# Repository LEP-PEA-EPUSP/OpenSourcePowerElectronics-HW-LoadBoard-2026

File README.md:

# OpenSourcePowerElectronics-HW-LoadBoard-2026

This repository contains the manuals, schematics, layouts and other files necessary to build and used the AC and DC load boards.

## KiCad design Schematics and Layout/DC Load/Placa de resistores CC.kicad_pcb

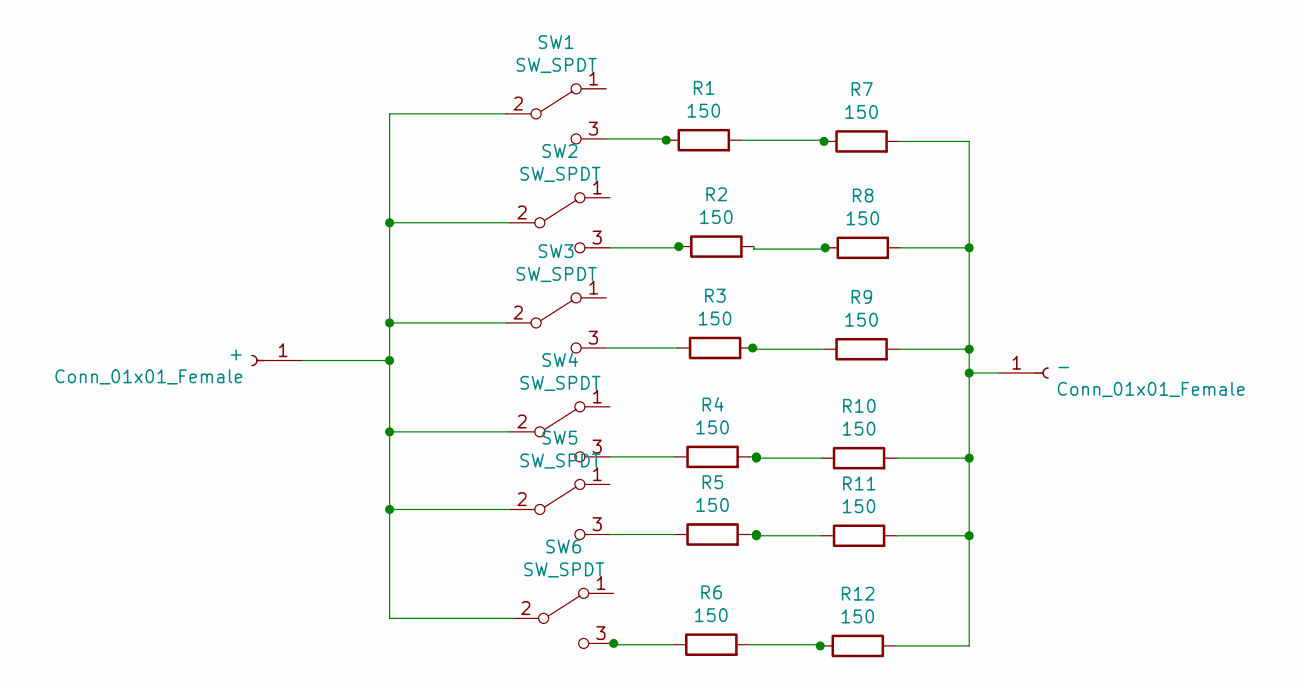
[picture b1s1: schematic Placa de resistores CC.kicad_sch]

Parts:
+: Conn_01x01_Female; Borne
-: Conn_01x01_Female; Borne
R1, R2, R3, R4, R5, R6, R7, R8, R9, R10, R11, R12: 150; Resistor_10W_porcelana
SW1, SW2, SW3, SW4, SW5, SW6: SW_SPDT; chave-hh

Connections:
unnamed: +.1, SW1.2 (B), SW2.2 (B), SW3.2 (B), SW4.2 (B), SW5.2 (B), SW6.2 (B)
unnamed: -.1, R7.2, R8.2, R9.2, R10.2, R11.2, R12.2
unnamed: R1.1, SW1.3 (C)
unnamed: R1.2, R7.1
unnamed: R2.1, SW2.3 (C)
unnamed: R2.2, R8.1
unnamed: R3.1, SW3.3 (C)
unnamed: R3.2, R9.1
unnamed: R4.1, SW4.3 (C)
unnamed: R5.1, SW5.3 (C)
unnamed: R6.1, SW6.3 (C)
unnamed: R4.2, R10.1
unnamed: R5.2, R11.1
unnamed: R6.2, R12.1

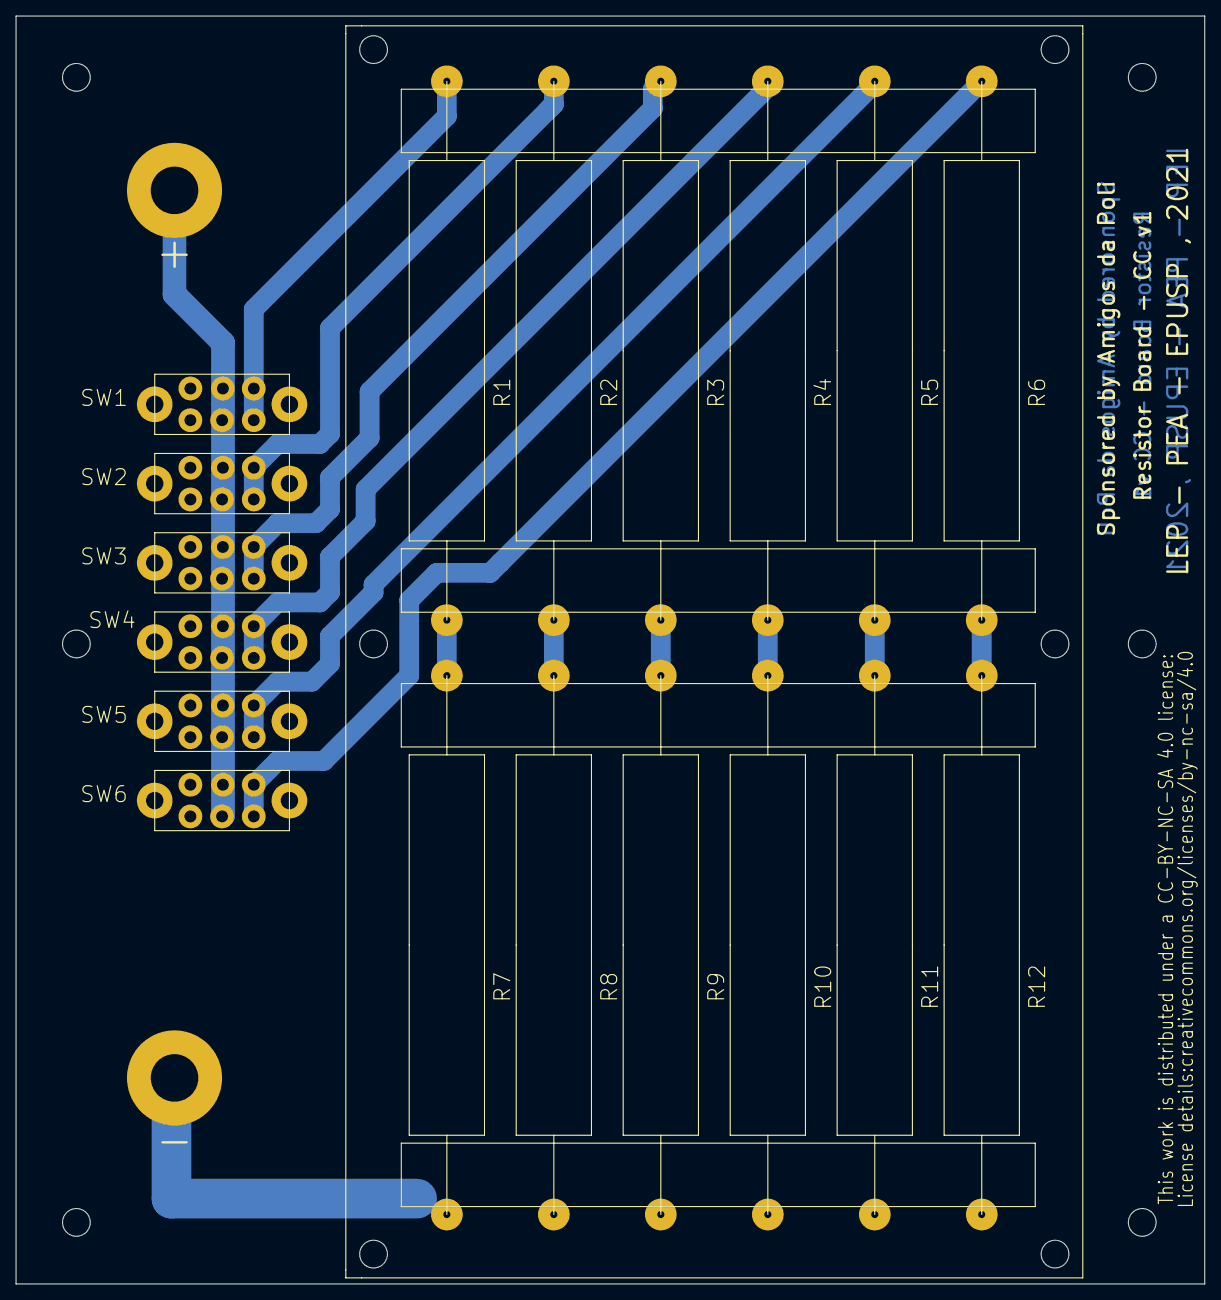
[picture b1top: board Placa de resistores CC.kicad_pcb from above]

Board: 2 copper layers, 150.0 x 160.0 mm, 20 parts (0 on the bottom side), 14 nets.

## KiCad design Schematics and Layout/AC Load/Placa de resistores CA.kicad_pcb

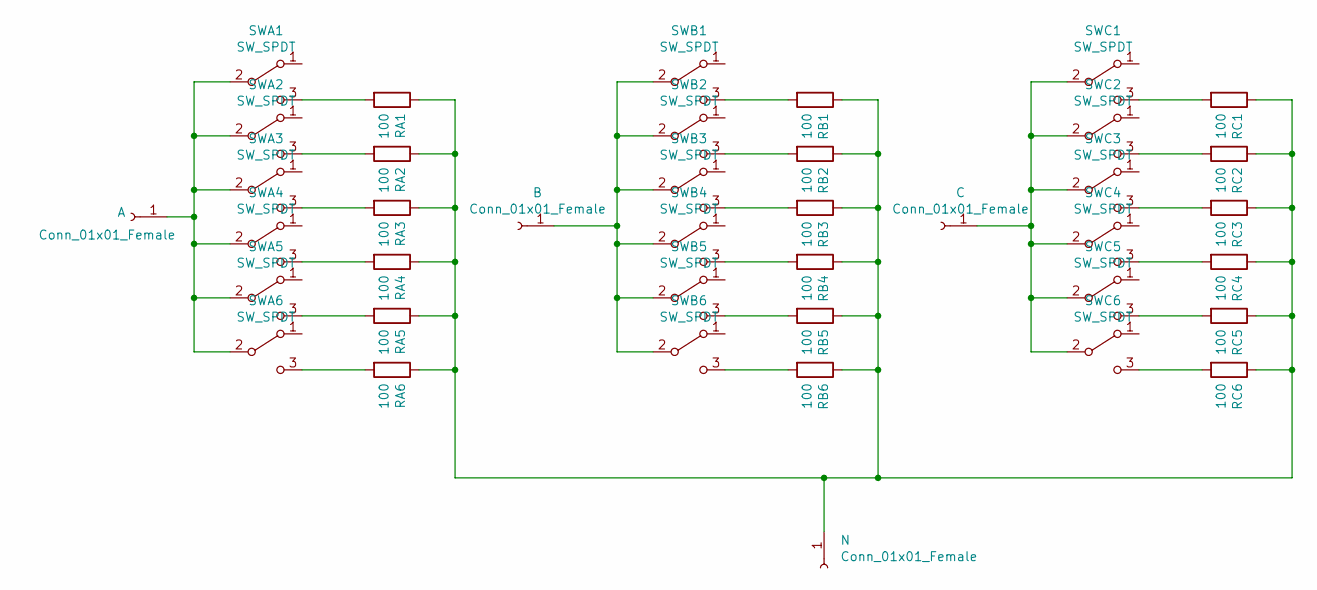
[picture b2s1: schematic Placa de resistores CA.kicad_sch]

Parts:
A: Conn_01x01_Female; Borne
B: Conn_01x01_Female; Borne
C: Conn_01x01_Female; Borne
N: Conn_01x01_Female; Borne
RA1, RA2, RA3, RA4, RA5, RA6: 100; Resistor_10W_porcelana
RB1, RB2, RB3, RB4, RB5, RB6: 100; Resistor_10W_porcelana
RC1, RC2, RC3, RC4, RC5, RC6: 100; Resistor_10W_porcelana
SWA1, SWA2, SWA3, SWA4, SWA5, SWA6: SW_SPDT; chave-hh
SWB1, SWB2, SWB3, SWB4, SWB5, SWB6: SW_SPDT; chave-hh
SWC1, SWC2, SWC3, SWC4, SWC5, SWC6: SW_SPDT; chave-hh

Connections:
unnamed: A.1, SWA1.2 (B), SWA2.2 (B), SWA3.2 (B), SWA4.2 (B), SWA5.2 (B), SWA6.2 (B)
unnamed: B.1, SWB1.2 (B), SWB2.2 (B), SWB3.2 (B), SWB4.2 (B), SWB5.2 (B), SWB6.2 (B)
unnamed: C.1, SWC1.2 (B), SWC2.2 (B), SWC3.2 (B), SWC4.2 (B), SWC5.2 (B), SWC6.2 (B)
unnamed: N.1, RA1.1, RA2.1, RA3.1, RA4.1, RA5.1, RA6.1, RB1.1, RB2.1, RB3.1, RB4.1, RB5.1, RB6.1, RC1.1, RC2.1, RC3.1, RC4.1, RC5.1, RC6.1
unnamed: RA1.2, SWA1.3 (C)
unnamed: RA2.2, SWA2.3 (C)
unnamed: RA3.2, SWA3.3 (C)
unnamed: RA4.2, SWA4.3 (C)
unnamed: RA5.2, SWA5.3 (C)
unnamed: RA6.2, SWA6.3 (C)
unnamed: RB1.2, SWB1.3 (C)
unnamed: RB2.2, SWB2.3 (C)
unnamed: RB3.2, SWB3.3 (C)
unnamed: RB4.2, SWB4.3 (C)
unnamed: RB5.2, SWB5.3 (C)
unnamed: RB6.2, SWB6.3 (C)
unnamed: RC1.2, SWC1.3 (C)
unnamed: RC2.2, SWC2.3 (C)
unnamed: RC3.2, SWC3.3 (C)
unnamed: RC4.2, SWC4.3 (C)
unnamed: RC5.2, SWC5.3 (C)
unnamed: RC6.2, SWC6.3 (C)

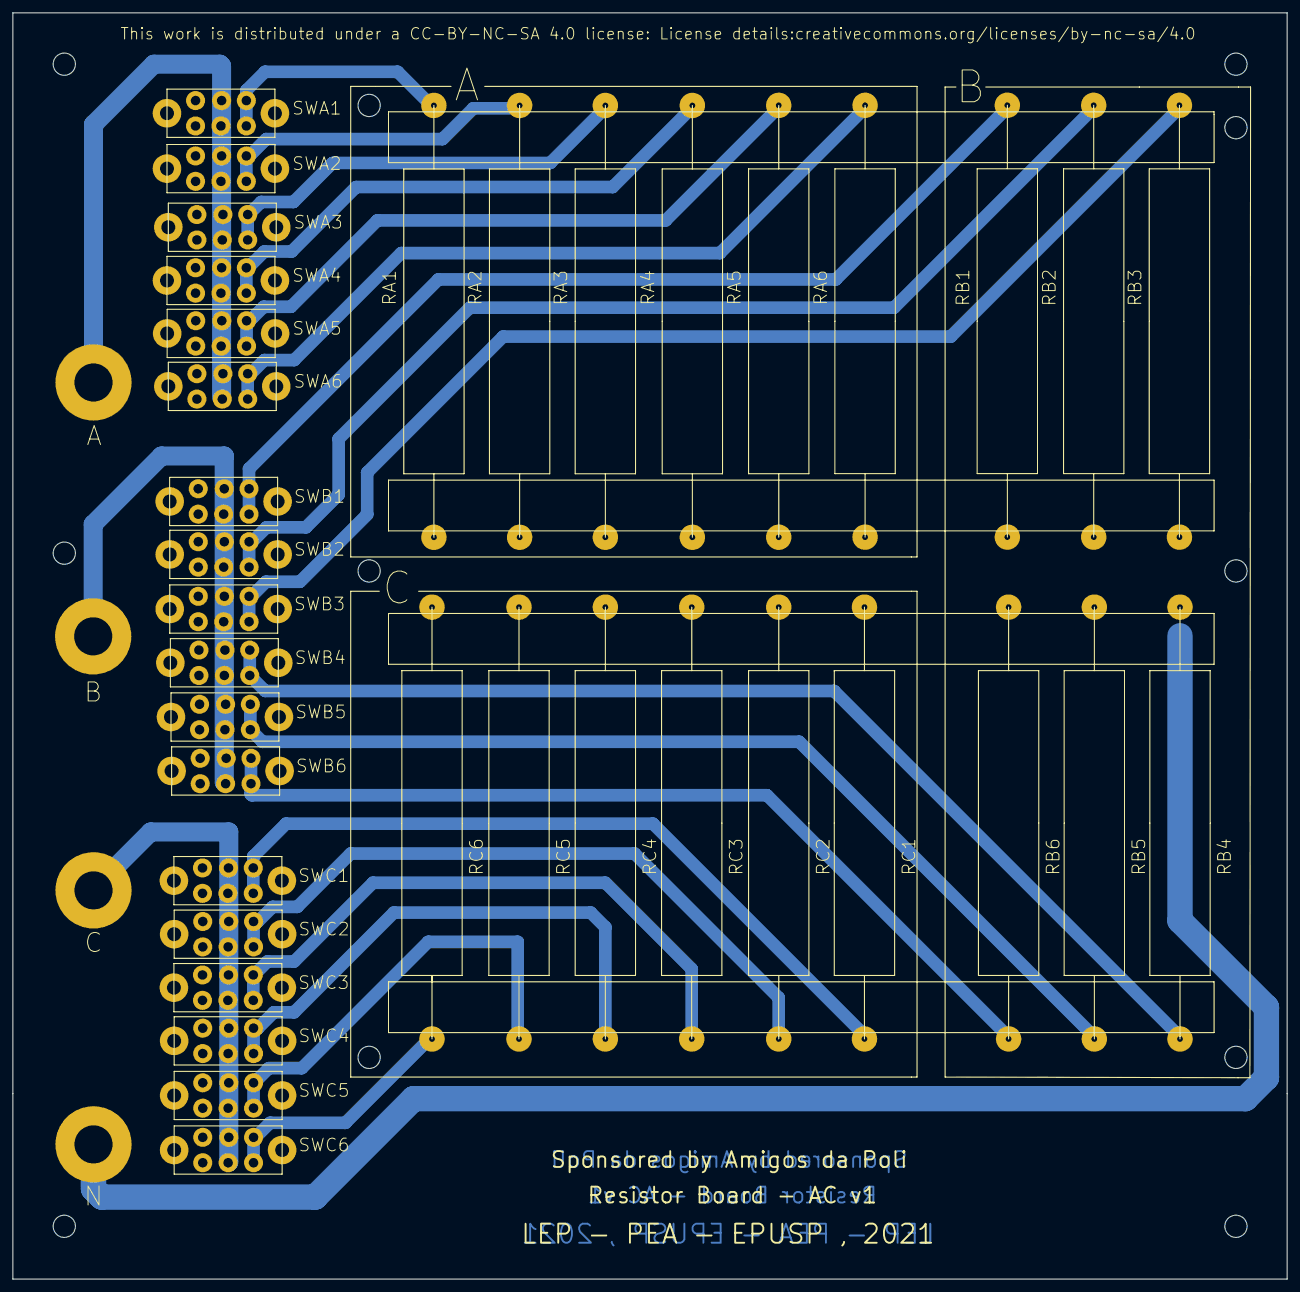
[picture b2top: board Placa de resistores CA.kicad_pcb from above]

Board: 2 copper layers, 200.7 x 199.4 mm, 40 parts (0 on the bottom side), 22 nets.

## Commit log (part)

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2026-06-18 Upload updated files

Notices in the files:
Schematics and Layout/AC Load/Placa de resistores CA.kicad_pcb:
This work is distributed under a CC-BY-NC-SA 4.0 license: License details:creativecommons.org/licenses/by-nc-sa/4.0
